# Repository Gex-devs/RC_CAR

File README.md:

# RC_CAR

ESP32 based RC Car using Xbox One Controller

## Components

## Software 

## Tools

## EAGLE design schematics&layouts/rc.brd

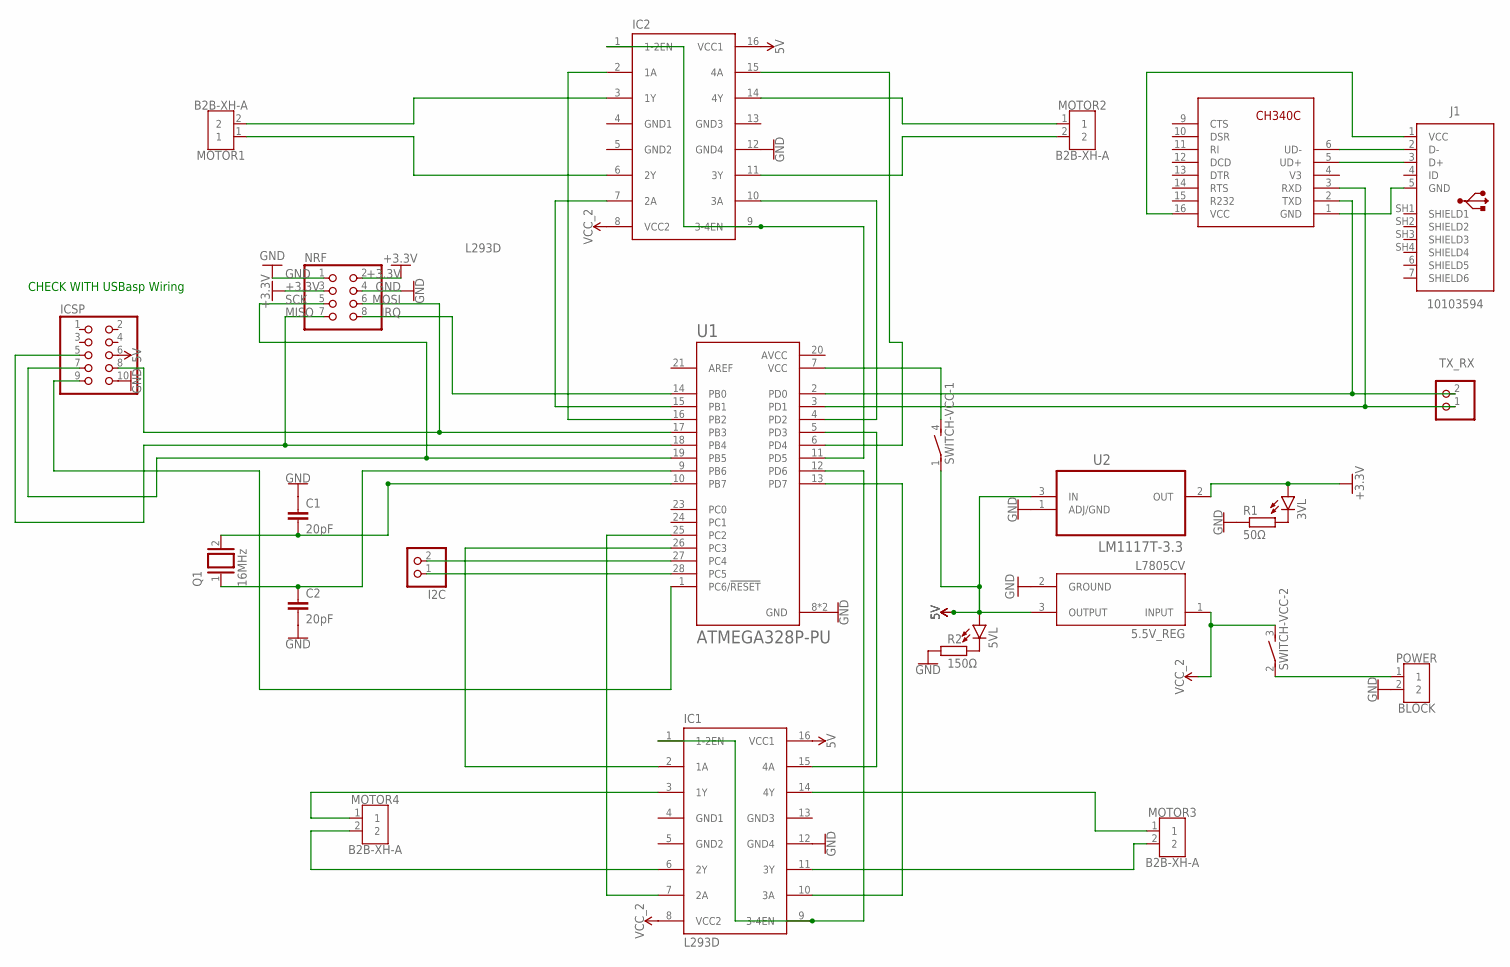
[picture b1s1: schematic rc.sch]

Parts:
3VL, 5VL: LED5MM
5.5V_REG: L7805CV; TO255P1040X460X1968-3
C1, C2: 20pF; C025-025X050
I2C: PINHD-1X2; 1X02
IC1, IC2: L293D; DIL16
ICSP: PINHD-2X5; 2X05
J1: 10103594
MOTOR1, MOTOR2, MOTOR3, MOTOR4: B2B-XH-A
NRF: PINHD-2X4; 2X04
POWER: BLOCK; TERMBLK_254-2N
Q1: 16MHz; QS
R1: 50Ω; 0204/7
R2: 150Ω; 0204/7
SWITCH-VCC: DS02E; DS-02
TX_RX: PINHD-1X2; 1X02
U1: ATMEGA328P-PU; DIP794W46P254L2967H457Q28B
U2: LM1117T-3.3; TO254P470X1016X2222-3P
U$1: CH340C; SOP16-1.27-10.0X5.0MM

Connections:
5V: 5.5V_REG.3 (OUTPUT), 5VL.A, IC1.16 (VCC1), IC2.16 (VCC1), ICSP.6, SWITCH-VCC.1, U2.3 (IN)
+3.3V: 3VL.A, NRF.2, NRF.3, U2.2 (OUT)
AVCC: U1.20 (AVCC)
GND: 5.5V_REG.2 (GROUND), C1.1, C2.2, IC1.12 (GND4), IC2.12 (GND4), ICSP.10, NRF.1, NRF.4, POWER.2, R1.1, R2.1, U1.8 (GND), U1.22 (GND), U2.1 (ADJ/GND)
GND1: IC1.4 (GND1), IC2.4 (GND1)
GND2: IC1.5 (GND2), IC2.5 (GND2)
GND3: IC1.13 (GND3), IC2.13 (GND3)
IRQ: NRF.8, U1.14 (PB0)
MISO: ICSP.5, NRF.7, U1.18 (PB4)
MOSI: ICSP.8, NRF.6, U1.17 (PB3)
unnamed: C1.2, Q1.2, U1.10 (PB7)
unnamed: J1.1 (VCC), U$1.16 (VCC)
unnamed: IC1.14 (4Y), MOTOR3.1
unnamed: IC1.11 (3Y), MOTOR3.2
unnamed: IC1.3 (1Y), MOTOR4.1
unnamed: IC1.6 (2Y), MOTOR4.2
unnamed: IC2.3 (1Y), MOTOR1.2
unnamed: IC2.6 (2Y), MOTOR1.1
unnamed: IC2.14 (4Y), MOTOR2.1
unnamed: IC2.11 (3Y), MOTOR2.2
unnamed: IC2.1 (1-2EN), IC2.9 (3-4EN), U1.11 (PD5)
unnamed: IC2.15 (4A), U1.6 (PD4)
unnamed: IC1.1 (1-2EN), IC1.9 (3-4EN), U1.12 (PD6)
unnamed: IC2.10 (3A), U1.4 (PD2)
unnamed: IC1.10 (3A), U1.13 (PD7)
unnamed: IC1.2 (1A), U1.26 (PC3)
unnamed: C2.1, Q1.1, U1.9 (PB6)
unnamed: I2C.2, U1.27 (PC4)
unnamed: I2C.1, U1.28 (PC5)
unnamed: 5VL.K (C), R2.2
unnamed: 3VL.K (C), R1.2
unnamed: J1.2 (D-), U$1.6 (UD-)
unnamed: J1.3 (D+), U$1.5 (UD+)
unnamed: POWER.1, SWITCH-VCC.2 (1)
unnamed: SWITCH-VCC.4 (2), U1.7 (VCC)
unnamed: J1.5 (GND), U$1.1 (GND)
unnamed: IC1.15 (4A), U1.5 (PD3)
unnamed: IC1.7 (2A), U1.25 (PC2)
unnamed: IC2.7 (2A), U1.15 (PB1)
unnamed: IC2.2 (1A), U1.16 (PB2)
RESET: ICSP.9, U1.1 (PC6/!RESET)
RX: TX_RX.2, U1.2 (PD0), U$1.2 (TXD)
SCK: ICSP.7, NRF.5, U1.19 (PB5)
TX: TX_RX.1, U1.3 (PD1), U$1.3 (RXD)
VCC_2: 5.5V_REG.1 (INPUT), IC1.8 (VCC2), IC2.8 (VCC2), SWITCH-VCC.3 (2)

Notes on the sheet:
CHECK WITH USBasp Wiring

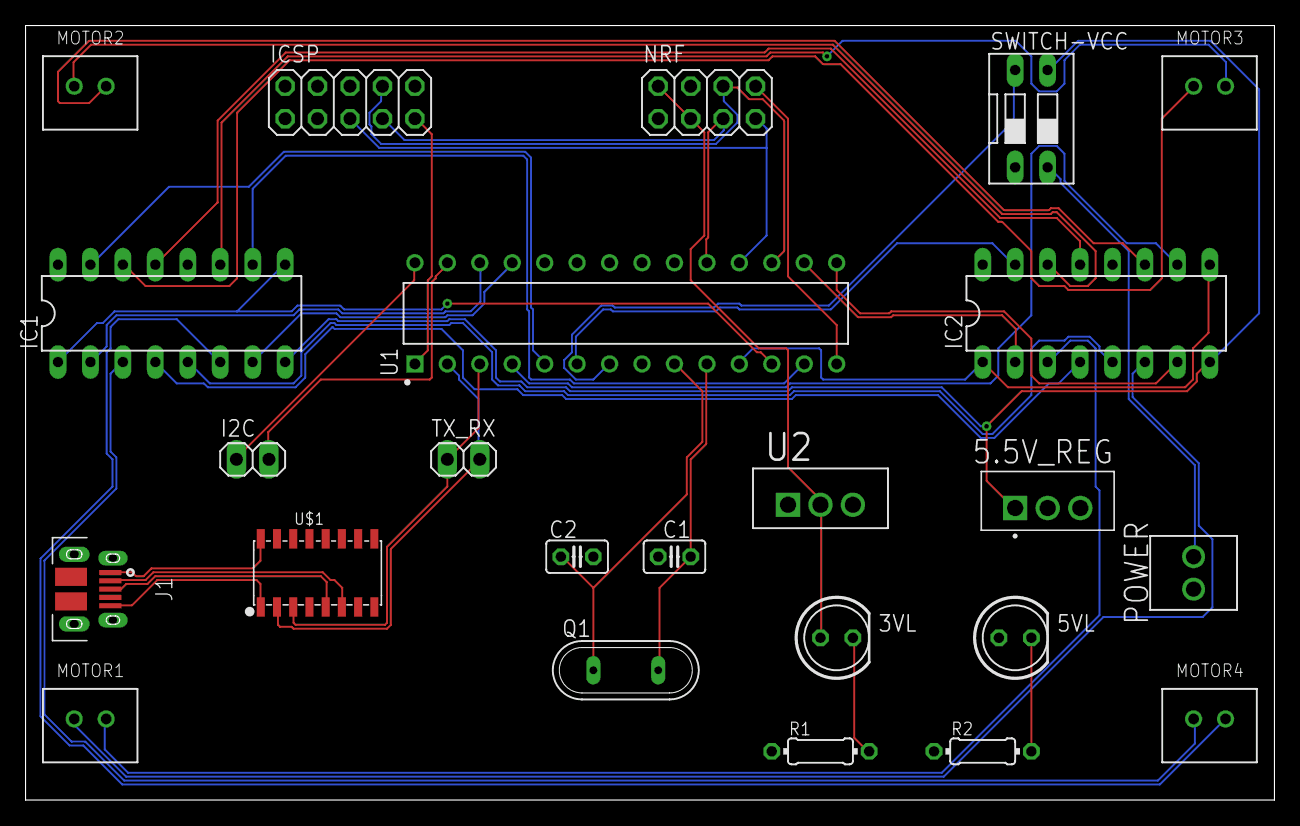
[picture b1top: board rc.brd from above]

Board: 4 copper layers, 97.8 x 60.6 mm, 24 parts (0 on the bottom side), 44 nets.

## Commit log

2023-04-15 organized
2023-04-18 adjusted configurations
2023-04-18 configured succ
2023-04-18 another succ
2023-04-23 added pics
2023-05-01 Working starter
2023-12-25 refractored env setup
2024-02-26 updated schematic
2024-02-28 updated eagle pcb schem
2024-03-19 update schematic
2024-03-20 updated schm
2024-05-02 Updated preview
2024-09-18 updated enviroment configuration for usbasp
2025-07-07 Updated Sch and moved from Eagle to Kicad
2025-08-11 Migrated to ESP32 and BLE
2025-08-13 Questionable Routing
2025-08-27 adjusted folder structure
2025-08-30 added dep
2025-08-30 added library
2025-08-30 removed modules
2025-08-30 added all required depencies and submodules. Compiles
2025-09-07 updated PCB Design and gitignore
2025-09-07 added workflow and updated ReadME(ish)
2025-09-07 workflow test
2025-09-07 who names their branch master???
2025-09-07 env is your best friend, workflow test 2
2025-09-07 Update schematic preview [skip ci]

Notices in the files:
parts and their libraries:
SparkFun-PowerSymbols: Licensing: Creative Commons ShareAlike 4.0 International - https://creativecommons.org/licenses/by-sa/4.0
